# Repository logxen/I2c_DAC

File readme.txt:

Bill of Materials:

 1 x 1"x1" single sided copper clad board

 1 x MCP4725
 2 x 10k 0204 smt resistors
 1 x 0.1uF 0204 smt capacitor
 1 x 4 pin 100mil single row header
 3 x 3 pin 100mil single row header
 2 x 100mil jumpers

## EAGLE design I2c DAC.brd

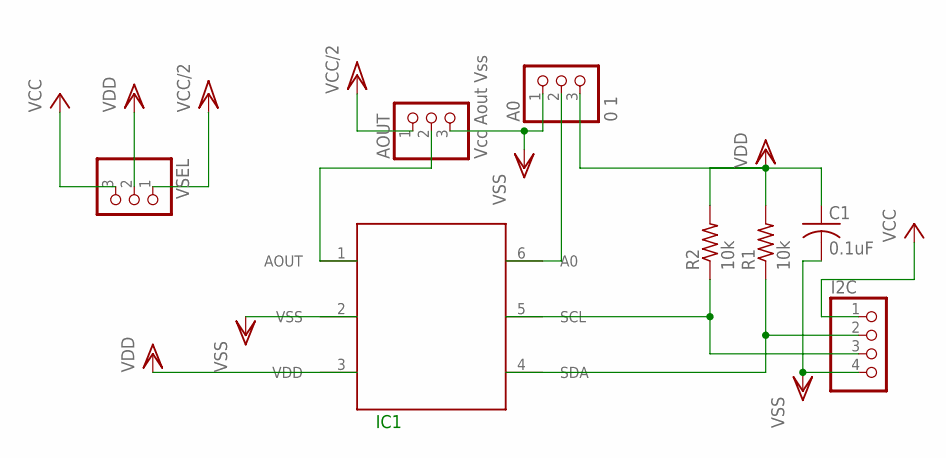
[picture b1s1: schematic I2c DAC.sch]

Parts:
A0: 0 1; 1X03
AOUT: Vcc Aout Vss; 1X03
C1: 0.1uF; C0402
I2C: PINHD-1X4; 1X04
IC1: MCP4725; SOT23-6
R1, R2: 10k; R0402
VSEL: PINHD-1X3; 1X03

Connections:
unnamed: A0.2, IC1.6 (A0)
unnamed: I2C.3, IC1.5 (SCL), R2.1
unnamed: I2C.2, IC1.4 (SDA), R1.1
unnamed: AOUT.2, IC1.1 (AOUT)
VCC: I2C.1, VSEL.3
VCC/2: AOUT.1, VSEL.1
VDD: A0.3, C1.1, IC1.3 (VDD), R1.2, R2.2, VSEL.2
VSS: A0.1, AOUT.3, C1.2, I2C.4, IC1.2 (VSS)

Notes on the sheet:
IC1

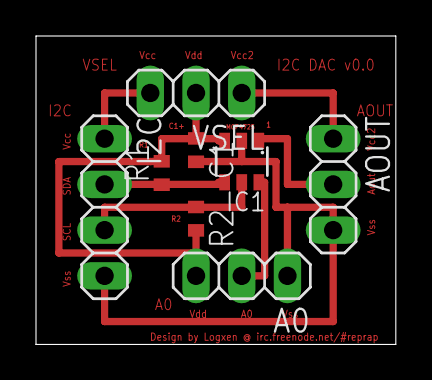
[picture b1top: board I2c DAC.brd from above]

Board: 1 copper layer, 20.0 x 17.1 mm, 8 parts (0 on the bottom side), 8 nets.

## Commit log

2012-06-22 Removed .gitignore and .gitattributes from the repo
2012-06-22 Added bitmap for actual top copper layer
